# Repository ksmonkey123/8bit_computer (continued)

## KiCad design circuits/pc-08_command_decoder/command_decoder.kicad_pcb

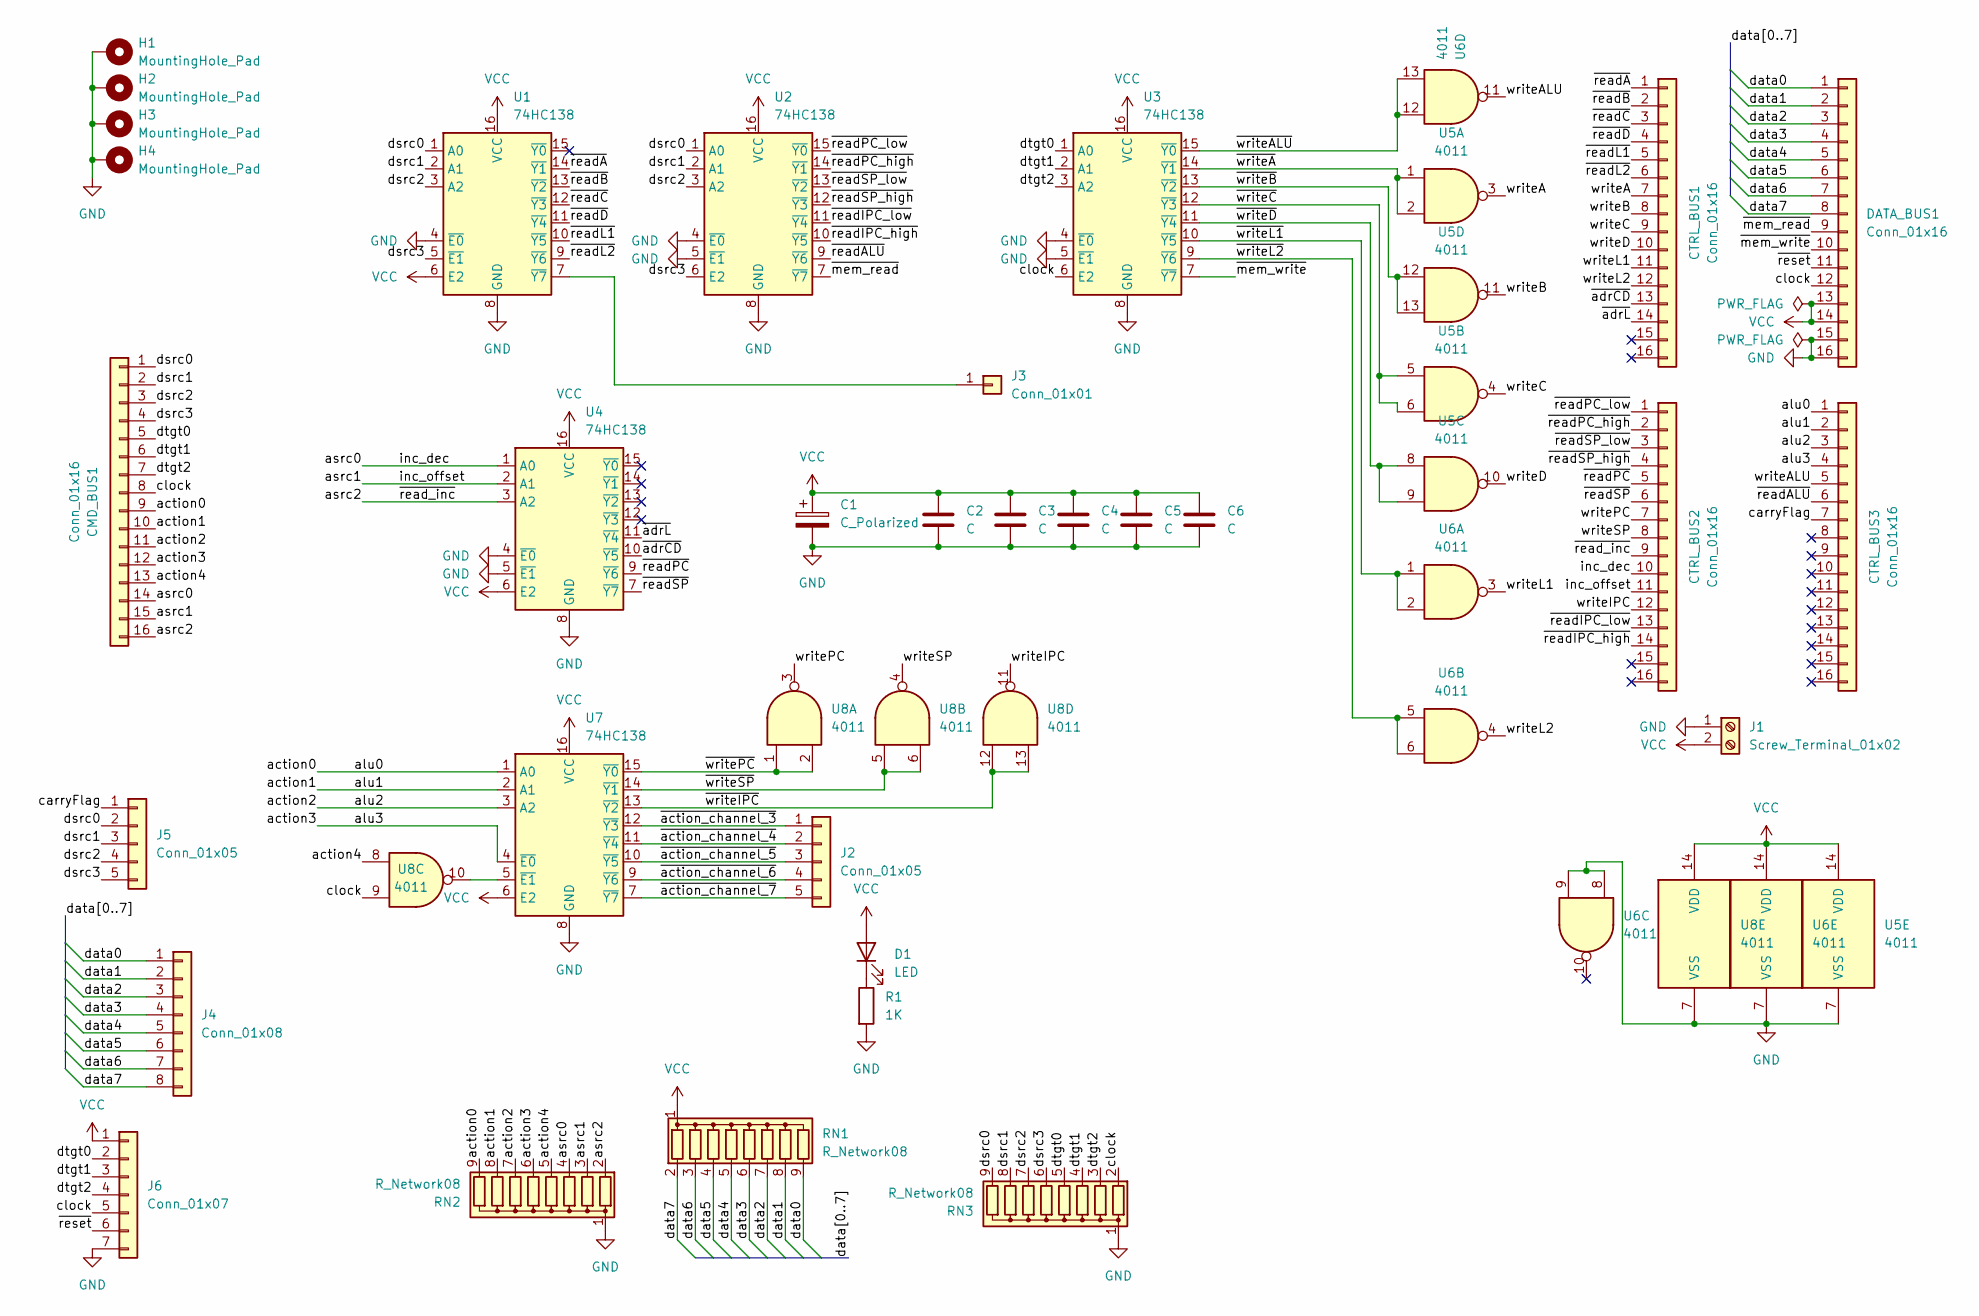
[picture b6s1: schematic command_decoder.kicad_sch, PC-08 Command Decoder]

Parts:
C1: C_Polarized; CP_Elec_5x5.3
C2, C3, C4, C5, C6: C; C_0603_1608Metric
CMD_BUS1: Conn_01x16; IDC-Header_2x08_P2.54mm_Horizontal
CTRL_BUS1, CTRL_BUS2, CTRL_BUS3: Conn_01x16; IDC-Header_2x08_P2.54mm_Vertical
D1: LED; LED_0603_1608Metric
DATA_BUS1: Conn_01x16; IDC-Header_2x08_P2.54mm_Horizontal
H1, H2, H3, H4: MountingHole_Pad; MountingHole_3.2mm_M3_Pad_Via
J1: Screw_Terminal_01x02; TerminalBlock_TE_282834-2_1x02_P2.54mm_Horizontal
J2, J5: Conn_01x05; PinHeader_1x05_P2.54mm_Vertical
J3: Conn_01x01; PinHeader_1x01_P2.54mm_Vertical
J4: Conn_01x08; PinHeader_1x08_P2.54mm_Vertical
J6: Conn_01x07; PinHeader_1x07_P2.54mm_Vertical
R1: 1K; R_0603_1608Metric
RN1, RN2, RN3: R_Network08; R_Array_SIP9
U1, U2, U3, U4, U7: 74HC138; DIP-16_W7.62mm_LongPads
U5, U6, U8: 4011; DIP-14_W7.62mm_LongPads

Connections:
/action0: CMD_BUS1.9, CTRL_BUS3.1, RN2.9 (R8), U7.1 (A0)
/action1: CMD_BUS1.10, CTRL_BUS3.2, RN2.8 (R7), U7.2 (A1)
/action2: CMD_BUS1.11, CTRL_BUS3.3, RN2.7 (R6), U7.3 (A2)
/action3: CMD_BUS1.12, CTRL_BUS3.4, RN2.6 (R5), U7.4 (~E0)
/action4: CMD_BUS1.13, RN2.5 (R4), U8.8
/asrc0: CMD_BUS1.14, CTRL_BUS2.10, RN2.4 (R3), U4.1 (A0)
/asrc1: CMD_BUS1.15, CTRL_BUS2.11, RN2.3 (R2), U4.2 (A1)
/asrc2: CMD_BUS1.16, CTRL_BUS2.9, RN2.2 (R1), U4.3 (A2)
/carryFlag: CTRL_BUS3.7, J5.1
/clock: CMD_BUS1.8, DATA_BUS1.12, J6.5, RN3.2 (R1), U3.6 (E2), U8.9
/data0: DATA_BUS1.1, J4.1, RN1.9 (R8)
/data1: DATA_BUS1.2, J4.2, RN1.8 (R7)
/data2: DATA_BUS1.3, J4.3, RN1.7 (R6)
/data3: DATA_BUS1.4, J4.4, RN1.6 (R5)
/data4: DATA_BUS1.5, J4.5, RN1.5 (R4)
/data5: DATA_BUS1.6, J4.6, RN1.4 (R3)
/data6: DATA_BUS1.7, J4.7, RN1.3 (R2)
/data7: DATA_BUS1.8, J4.8, RN1.2 (R1)
/dsrc0: CMD_BUS1.1, J5.2, RN3.9 (R8), U1.1 (A0), U2.1 (A0)
/dsrc1: CMD_BUS1.2, J5.3, RN3.8 (R7), U1.2 (A1), U2.2 (A1)
/dsrc2: CMD_BUS1.3, J5.4, RN3.7 (R6), U1.3 (A2), U2.3 (A2)
/dsrc3: CMD_BUS1.4, J5.5, RN3.6 (R5), U1.5 (~E1), U2.6 (E2)
/dtgt0: CMD_BUS1.5, J6.2, RN3.5 (R4), U3.1 (A0)
/dtgt1: CMD_BUS1.6, J6.3, RN3.4 (R3), U3.2 (A1)
/dtgt2: CMD_BUS1.7, J6.4, RN3.3 (R2), U3.3 (A2)
/writeA: CTRL_BUS1.7, U5.3
/writeALU: CTRL_BUS3.5, U6.11
/writeB: CTRL_BUS1.8, U5.11
/writeC: CTRL_BUS1.9, U5.4
/writeD: CTRL_BUS1.10, U5.10
/writeIPC: CTRL_BUS2.12, U8.11
/writeL1: CTRL_BUS1.11, U6.3
/writeL2: CTRL_BUS1.12, U6.4
/writePC: CTRL_BUS2.7, U8.3
/writeSP: CTRL_BUS2.8, U8.4
/~action_channel_3: J2.1, U7.12 (~Y3)
/~action_channel_4: J2.2, U7.11 (~Y4)
/~action_channel_5: J2.3, U7.10 (~Y5)
/~action_channel_6: J2.4, U7.9 (~Y6)
/~action_channel_7: J2.5, U7.7 (~Y7)
/~adrCD: CTRL_BUS1.13, U4.10 (~Y5)
/~adrL: CTRL_BUS1.14, U4.11 (~Y4)
/~mem_read: DATA_BUS1.9, U2.7 (~Y7)
/~mem_write: DATA_BUS1.10, U3.7 (~Y7)
/~readALU: CTRL_BUS3.6, U2.9 (~Y6)
/~readA: CTRL_BUS1.1, U1.14 (~Y1)
/~readB: CTRL_BUS1.2, U1.13 (~Y2)
/~readC: CTRL_BUS1.3, U1.12 (~Y3)
/~readD: CTRL_BUS1.4, U1.11 (~Y4)
/~readIPC_high: CTRL_BUS2.14, U2.10 (~Y5)
/~readIPC_low: CTRL_BUS2.13, U2.11 (~Y4)
/~readL1: CTRL_BUS1.5, U1.10 (~Y5)
/~readL2: CTRL_BUS1.6, U1.9 (~Y6)
/~readPC_high: CTRL_BUS2.2, U2.14 (~Y1)
/~readPC_low: CTRL_BUS2.1, U2.15 (~Y0)
/~readPC: CTRL_BUS2.5, U4.9 (~Y6)
/~readSP_high: CTRL_BUS2.4, U2.12 (~Y3)
/~readSP_low: CTRL_BUS2.3, U2.13 (~Y2)
/~readSP: CTRL_BUS2.6, U4.7 (~Y7)
/~reset: DATA_BUS1.11, J6.6
/~writeALU: U3.15 (~Y0), U6.12, U6.13
/~writeA: U3.14 (~Y1), U5.1, U5.2
/~writeB: U3.13 (~Y2), U5.12, U5.13
/~writeC: U3.12 (~Y3), U5.5, U5.6
/~writeD: U3.11 (~Y4), U5.8, U5.9
/~writeIPC: U7.13 (~Y2), U8.12, U8.13
/~writeL1: U3.10 (~Y5), U6.1, U6.2
/~writeL2: U3.9 (~Y6), U6.5, U6.6
/~writePC: U7.15 (~Y0), U8.1, U8.2
/~writeSP: U7.14 (~Y1), U8.5, U8.6
GND: C1.2, C2.2, C3.2, C4.2, C5.2, C6.2, DATA_BUS1.15, DATA_BUS1.16, H1.1, H2.1, H3.1, H4.1, J1.1, J6.7, R1.2, RN2.1 (common), RN3.1 (common), U1.4 (~E0), U1.8 (GND), U2.4 (~E0), U2.5 (~E1), U2.8 (GND), U3.4 (~E0), U3.5 (~E1), U3.8 (GND), U4.4 (~E0), U4.5 (~E1), U4.8 (GND), U5.7 (VSS), U6.7 (VSS), U6.8, U6.9, U7.8 (GND), U8.7 (VSS)
unnamed: D1.1 (K), R1.1
unnamed: J3.1, U1.7 (~Y7)
unnamed: U7.5 (~E1), U8.10
VCC: C1.1, C2.1, C3.1, C4.1, C5.1, C6.1, D1.2 (A), DATA_BUS1.13, DATA_BUS1.14, J1.2, J6.1, RN1.1 (common), U1.6 (E2), U1.16 (VCC), U2.16 (VCC), U3.16 (VCC), U4.6 (E2), U4.16 (VCC), U5.14 (VDD), U6.14 (VDD), U7.6 (E2), U7.16 (VCC), U8.14 (VDD)

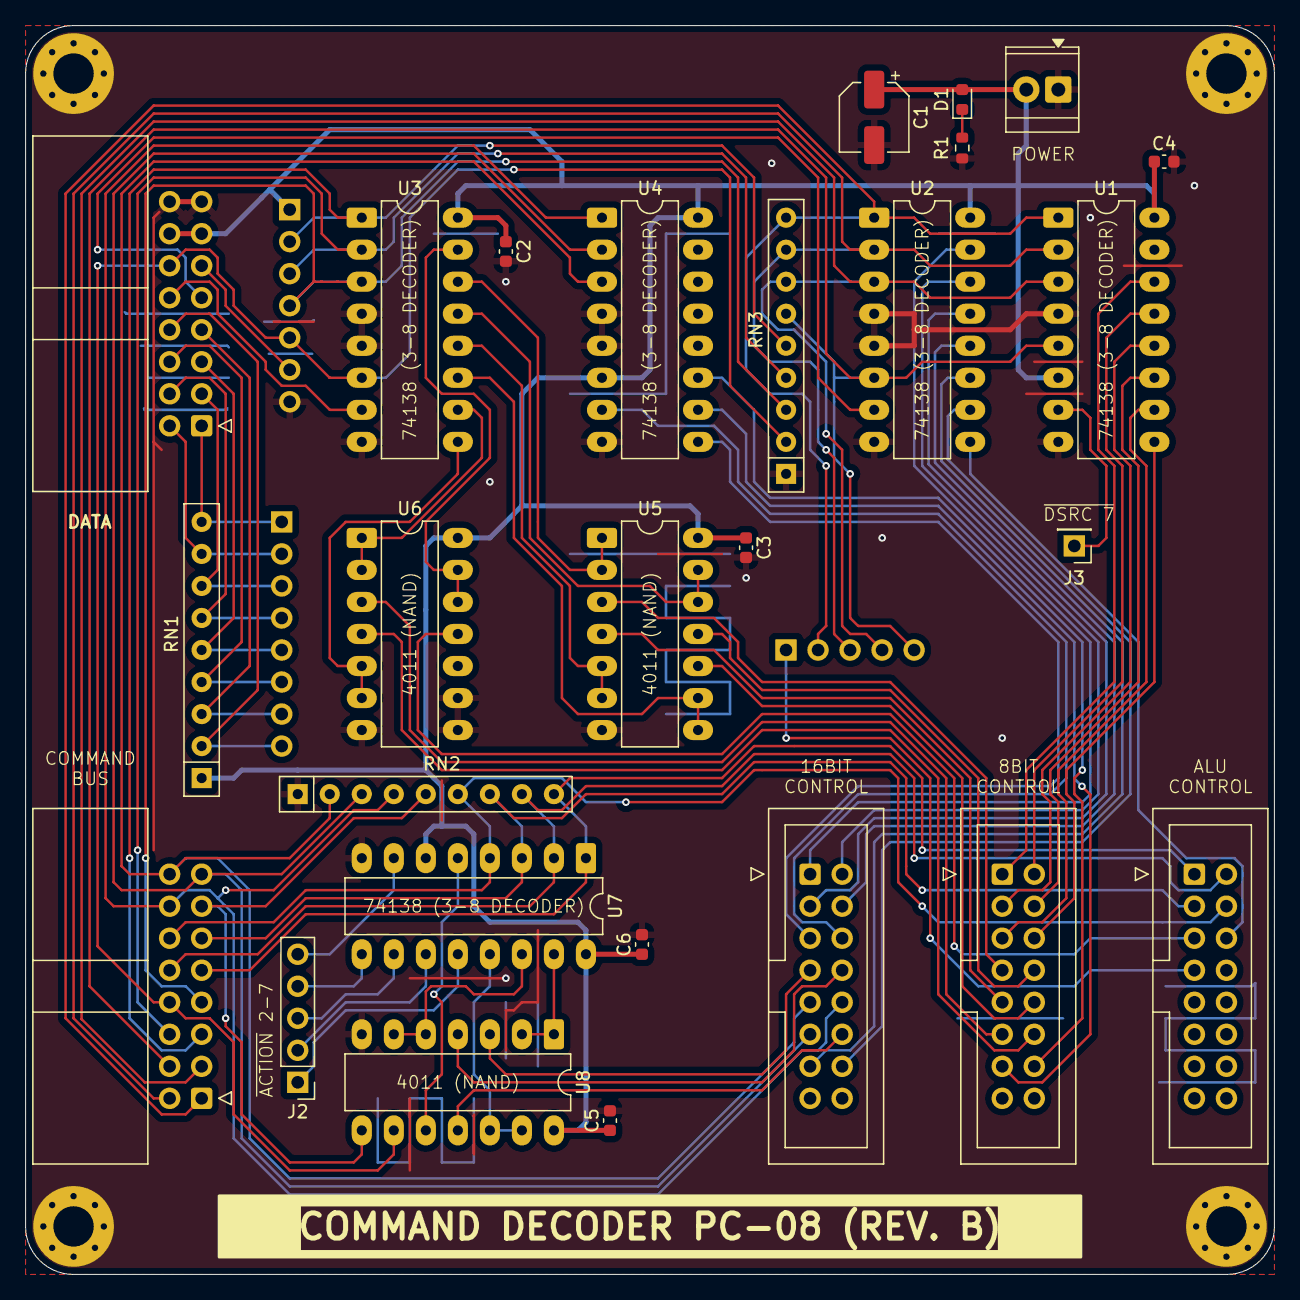
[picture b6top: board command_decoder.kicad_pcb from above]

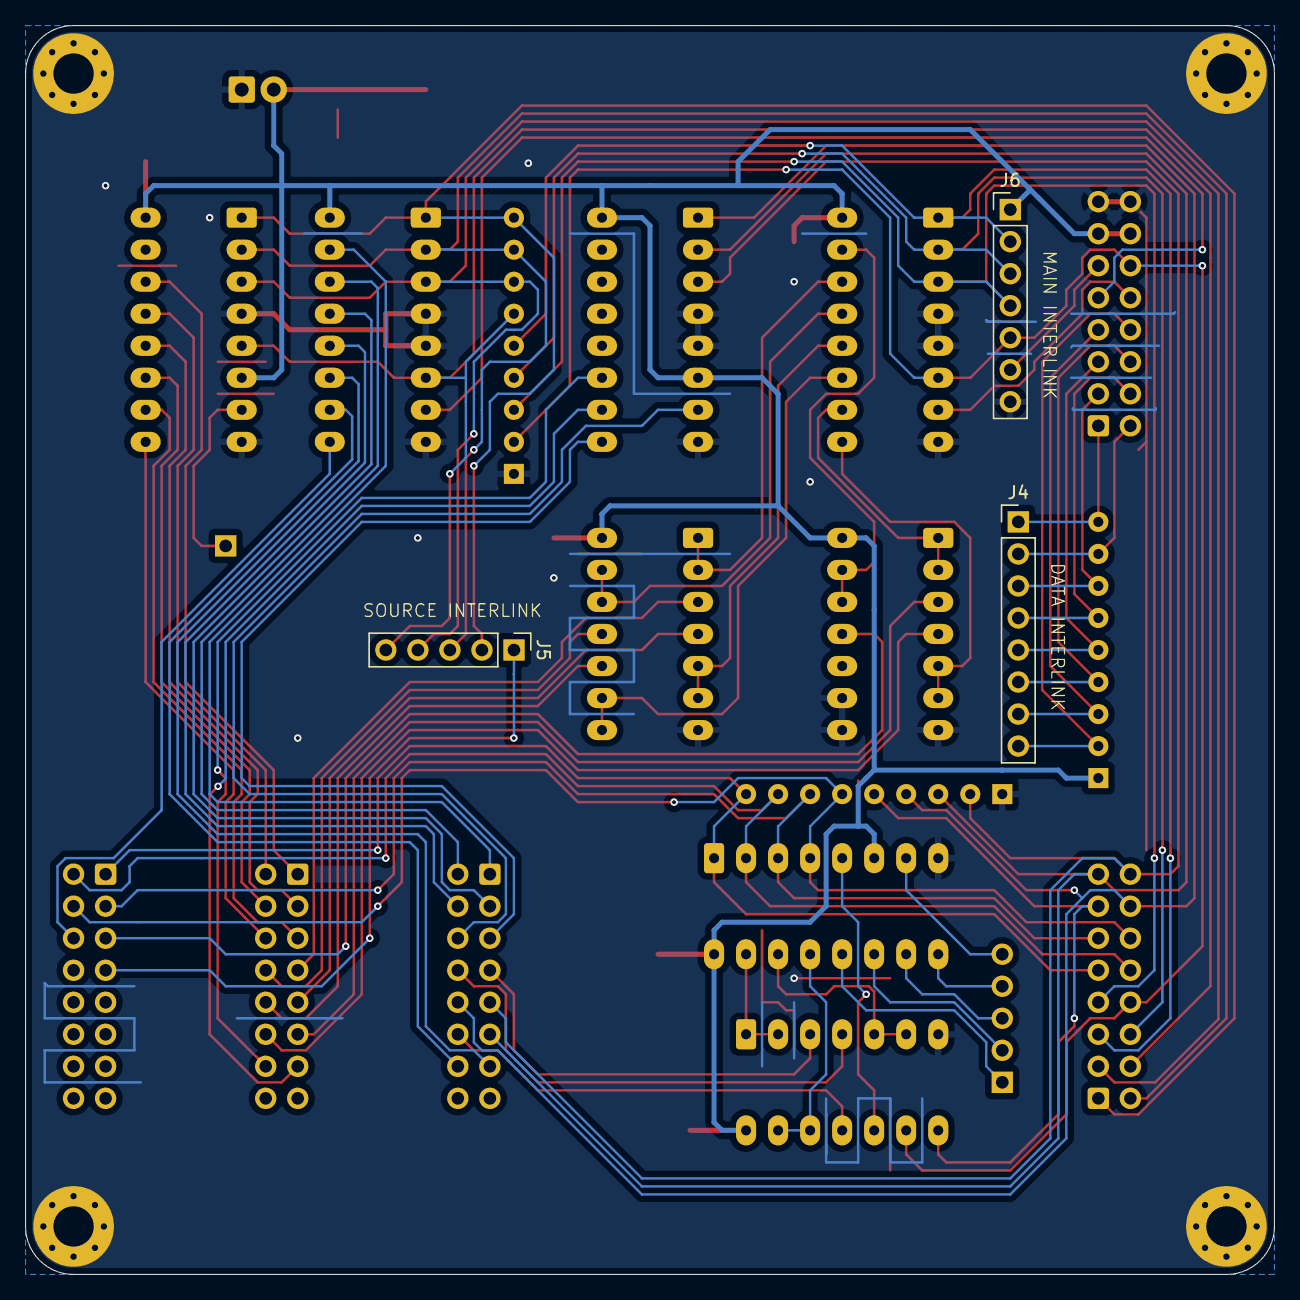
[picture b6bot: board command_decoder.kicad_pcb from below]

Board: 2 copper layers, 99.1 x 99.1 mm, 34 parts (3 on the bottom side), 75 nets.

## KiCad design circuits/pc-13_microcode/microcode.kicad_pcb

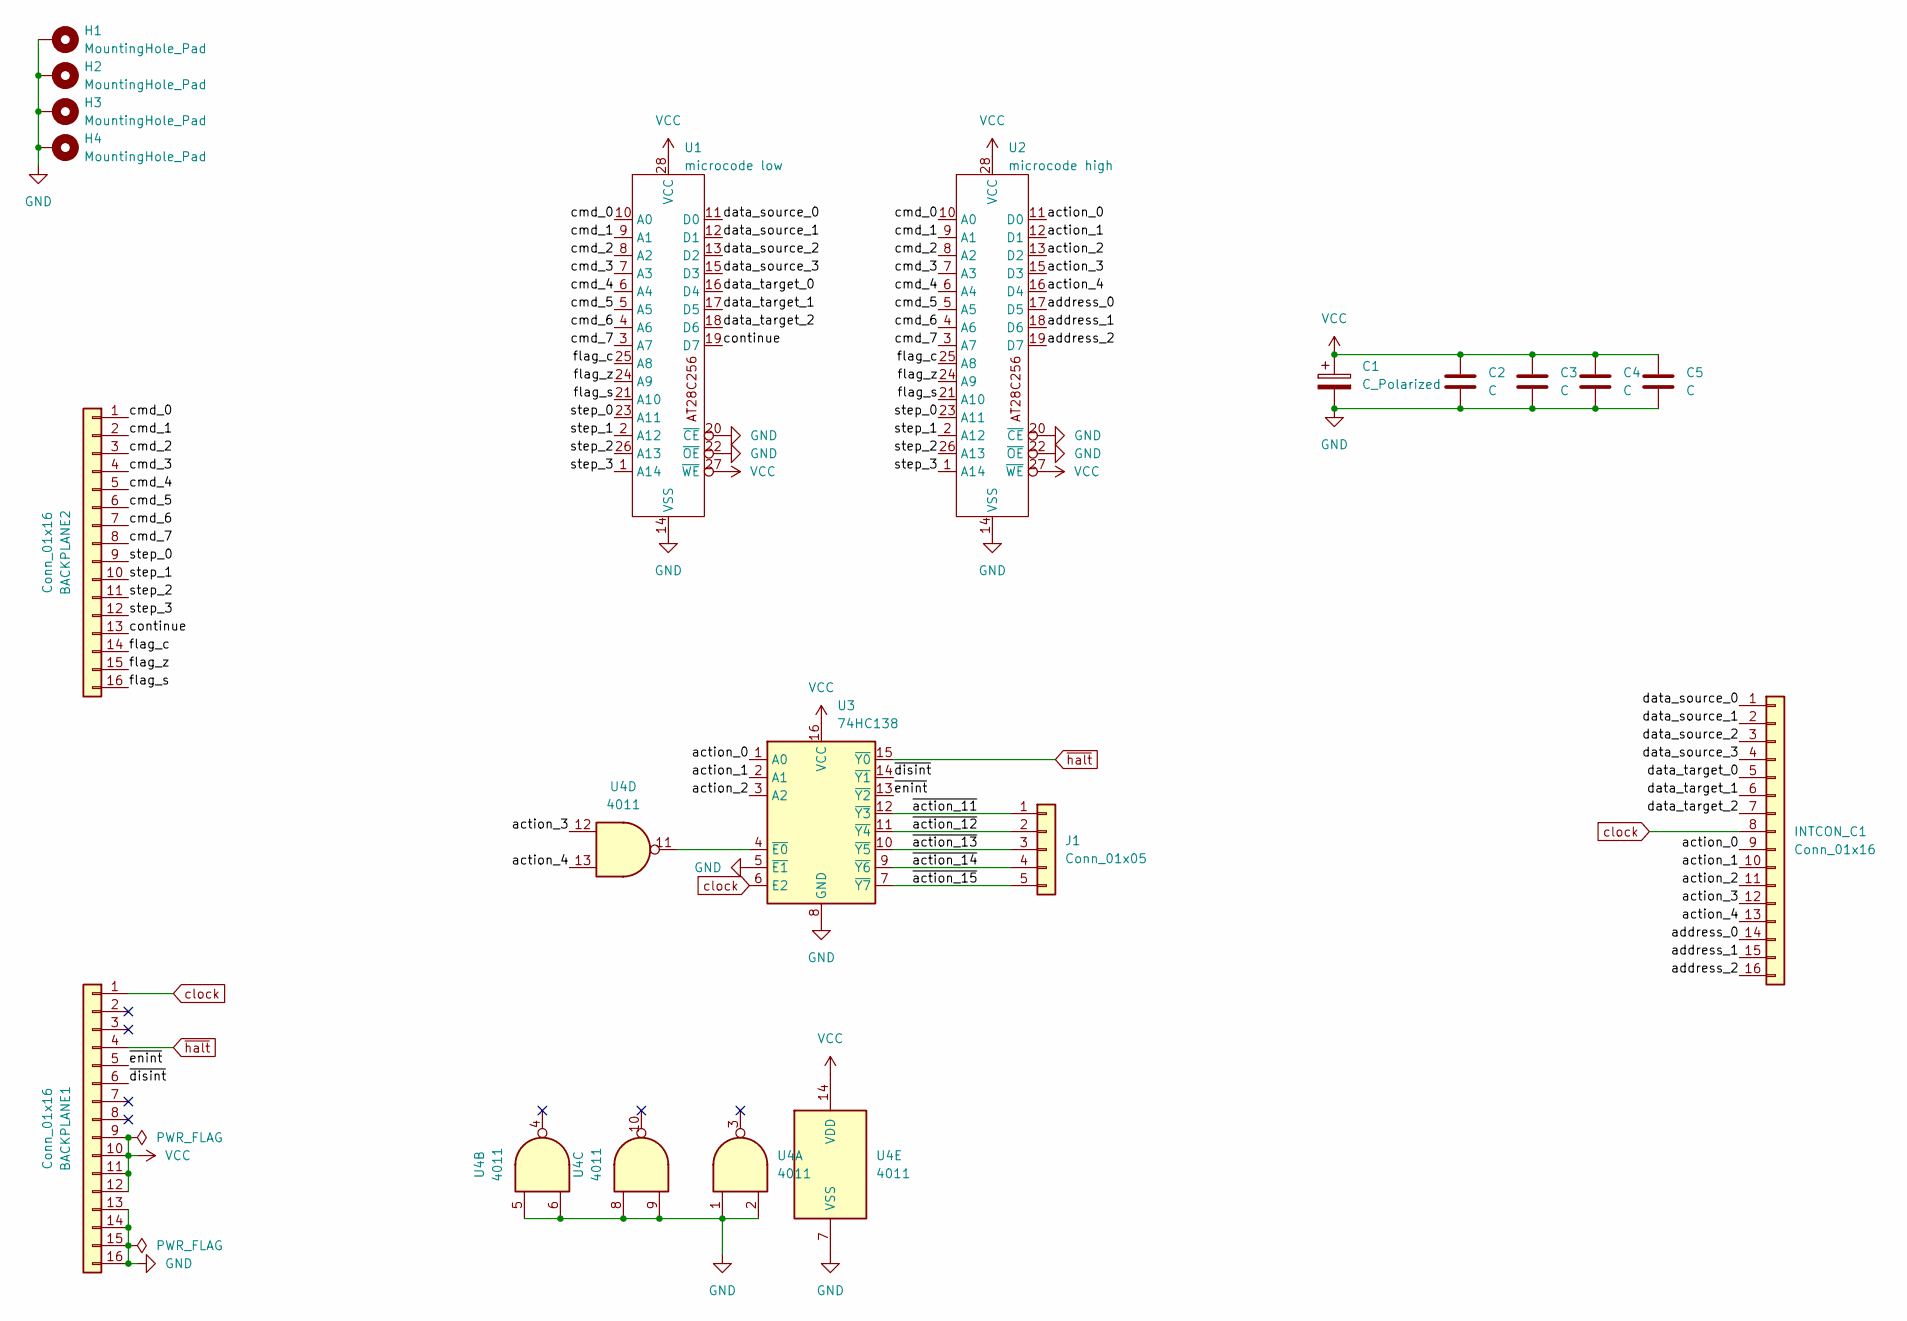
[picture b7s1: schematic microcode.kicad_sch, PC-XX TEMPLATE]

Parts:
BACKPLANE1, BACKPLANE2: Conn_01x16; IDC-Header_2x08_P2.54mm_Horizontal
C1: C_Polarized; CP_Elec_5x5.3
C2, C3, C4, C5: C; C_0603_1608Metric
H1, H2, H3, H4: MountingHole_Pad; MountingHole_3.2mm_M3_Pad_Via
INTCON_C1: Conn_01x16; IDC-Header_2x08_P2.54mm_Horizontal
J1: Conn_01x05; PinHeader_1x05_P2.54mm_Vertical
U1: microcode low; DIP-28_600_ELL
U2: microcode high; DIP-28_600_ELL
U3: 74HC138; DIP-16_W7.62mm
U4: 4011; DIP-14_W7.62mm

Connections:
/action_0: INTCON_C1.9, U2.11 (D0), U3.1 (A0)
/action_1: INTCON_C1.10, U2.12 (D1), U3.2 (A1)
/action_2: INTCON_C1.11, U2.13 (D2), U3.3 (A2)
/action_3: INTCON_C1.12, U2.15 (D3), U4.12
/action_4: INTCON_C1.13, U2.16 (D4), U4.13
/address_0: INTCON_C1.14, U2.17 (D5)
/address_1: INTCON_C1.15, U2.18 (D6)
/address_2: INTCON_C1.16, U2.19 (D7)
/cmd_0: BACKPLANE2.1, U1.10 (A0), U2.10 (A0)
/cmd_1: BACKPLANE2.2, U1.9 (A1), U2.9 (A1)
/cmd_2: BACKPLANE2.3, U1.8 (A2), U2.8 (A2)
/cmd_3: BACKPLANE2.4, U1.7 (A3), U2.7 (A3)
/cmd_4: BACKPLANE2.5, U1.6 (A4), U2.6 (A4)
/cmd_5: BACKPLANE2.6, U1.5 (A5), U2.5 (A5)
/cmd_6: BACKPLANE2.7, U1.4 (A6), U2.4 (A6)
/cmd_7: BACKPLANE2.8, U1.3 (A7), U2.3 (A7)
/continue: BACKPLANE2.13, U1.19 (D7)
/data_source_0: INTCON_C1.1, U1.11 (D0)
/data_source_1: INTCON_C1.2, U1.12 (D1)
/data_source_2: INTCON_C1.3, U1.13 (D2)
/data_source_3: INTCON_C1.4, U1.15 (D3)
/data_target_0: INTCON_C1.5, U1.16 (D4)
/data_target_1: INTCON_C1.6, U1.17 (D5)
/data_target_2: INTCON_C1.7, U1.18 (D6)
/flag_c: BACKPLANE2.14, U1.25 (A8), U2.25 (A8)
/flag_s: BACKPLANE2.16, U1.21 (A10), U2.21 (A10)
/flag_z: BACKPLANE2.15, U1.24 (A9), U2.24 (A9)
/step_0: BACKPLANE2.9, U1.23 (A11), U2.23 (A11)
/step_1: BACKPLANE2.10, U1.2 (A12), U2.2 (A12)
/step_2: BACKPLANE2.11, U1.26 (A13), U2.26 (A13)
/step_3: BACKPLANE2.12, U1.1 (A14), U2.1 (A14)
/~action_11: J1.1, U3.12 (~Y3)
/~action_12: J1.2, U3.11 (~Y4)
/~action_13: J1.3, U3.10 (~Y5)
/~action_14: J1.4, U3.9 (~Y6)
/~action_15: J1.5, U3.7 (~Y7)
/~disint: BACKPLANE1.6, U3.14 (~Y1)
/~enint: BACKPLANE1.5, U3.13 (~Y2)
GND: BACKPLANE1.13, BACKPLANE1.14, BACKPLANE1.15, BACKPLANE1.16, C1.2, C2.2, C3.2, C4.2, C5.2, H1.1, H2.1, H3.1, H4.1, U1.14 (VSS), U1.20 (~CE), U1.22 (~OE), U2.14 (VSS), U2.20 (~CE), U2.22 (~OE), U3.5 (~E1), U3.8 (GND), U4.1, U4.2, U4.5, U4.6, U4.7 (VSS), U4.8, U4.9
unnamed: U3.4 (~E0), U4.11
VCC: BACKPLANE1.9, BACKPLANE1.10, BACKPLANE1.11, BACKPLANE1.12, C1.1, C2.1, C3.1, C4.1, C5.1, U1.27 (~WE), U1.28 (VCC), U2.27 (~WE), U2.28 (VCC), U3.16 (VCC), U4.14 (VDD)
clock: BACKPLANE1.1, INTCON_C1.8, U3.6 (E2)
~halt: BACKPLANE1.4, U3.15 (~Y0)

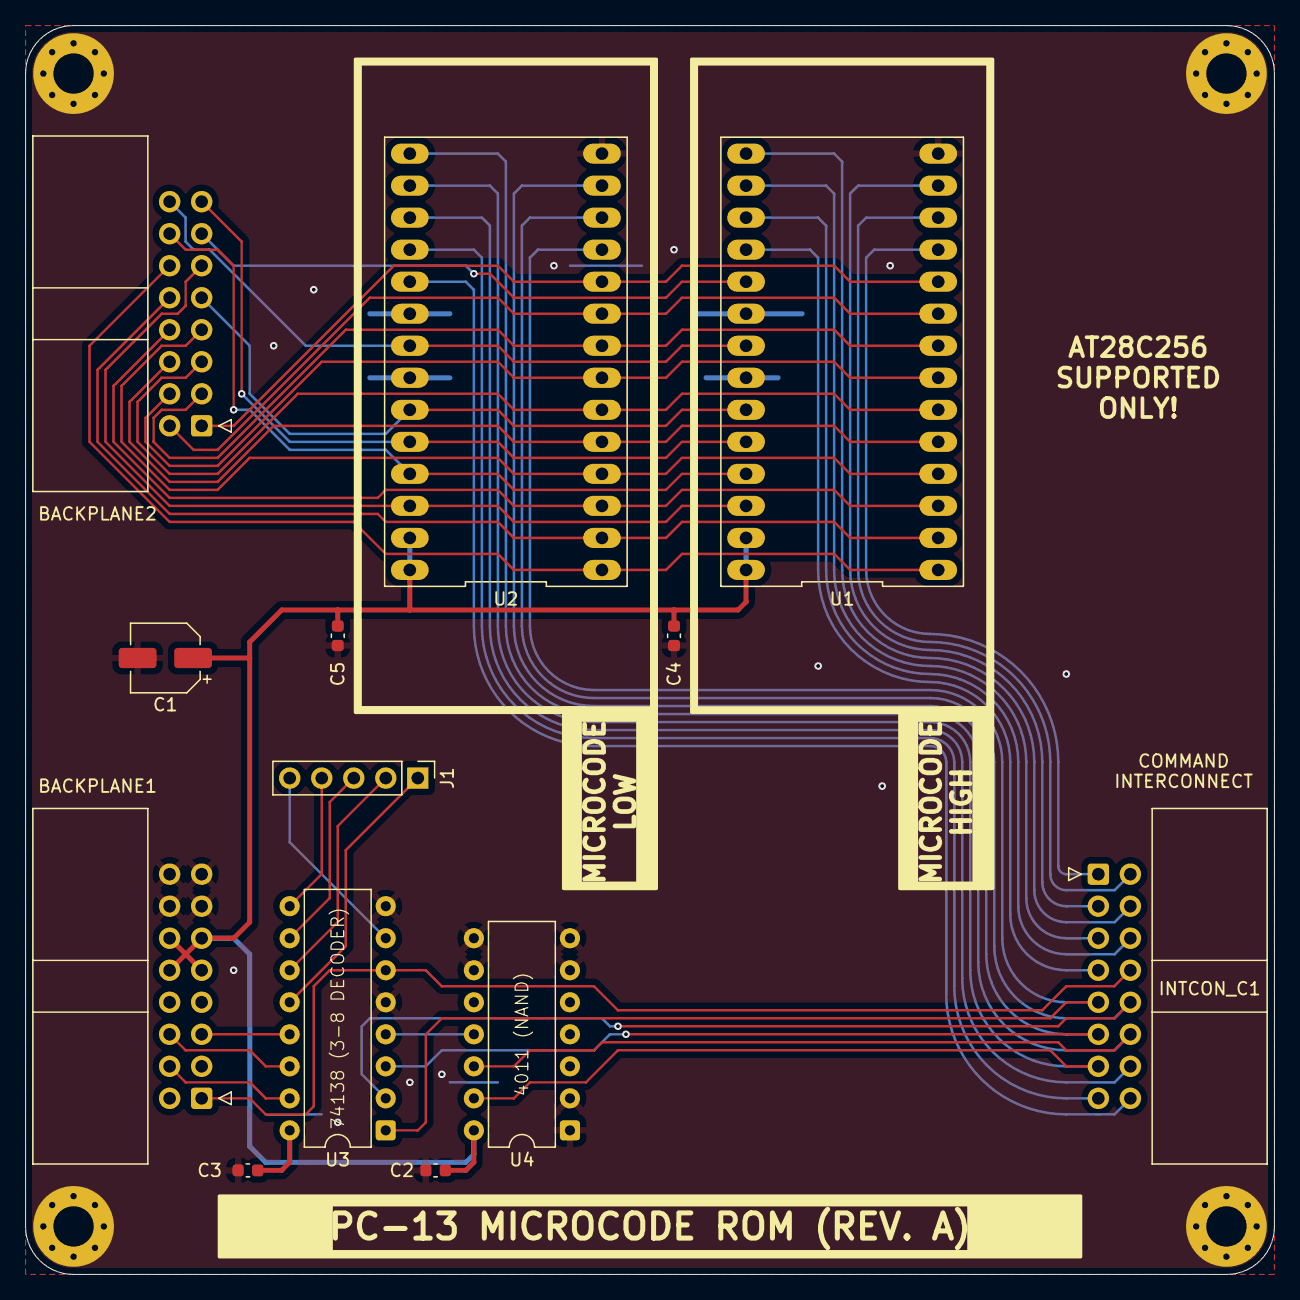
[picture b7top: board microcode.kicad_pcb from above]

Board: 2 copper layers, 99.1 x 99.1 mm, 17 parts (0 on the bottom side), 43 nets.

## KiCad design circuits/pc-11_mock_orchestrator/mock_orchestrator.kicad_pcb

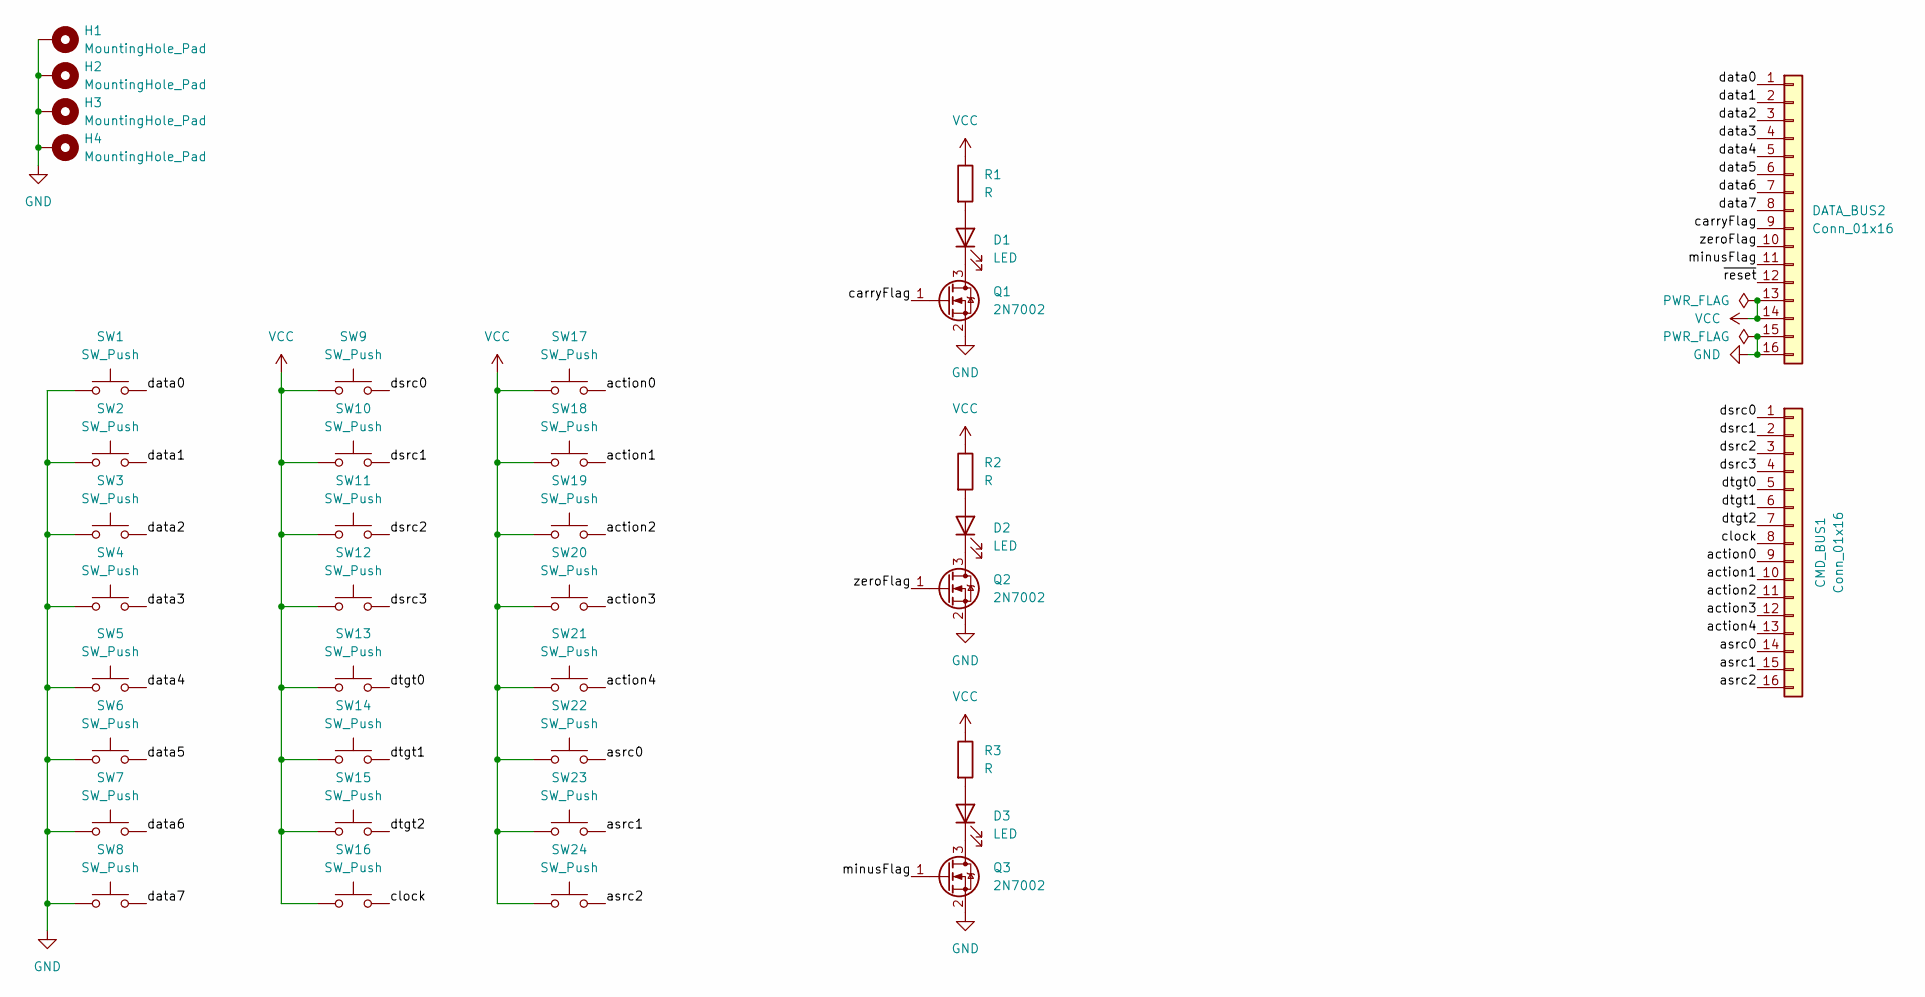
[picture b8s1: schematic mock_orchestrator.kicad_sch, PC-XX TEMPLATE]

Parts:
CMD_BUS1: Conn_01x16; IDC-Header_2x08_P2.54mm_Vertical
D1, D2, D3: LED; LED_0603_1608Metric
DATA_BUS2: Conn_01x16; IDC-Header_2x08_P2.54mm_Vertical
H1, H2, H3, H4: MountingHole_Pad; MountingHole_3.2mm_M3_Pad_Via
Q1, Q2, Q3: 2N7002; SOT-23
R1, R2, R3: R; R_0603_1608Metric
SW1, SW2, SW3, SW4, SW5, SW6, SW7, SW8, SW9, SW10, SW11, SW12, SW13, SW14, SW15, SW16, SW17, SW18, SW19, SW20, SW21, SW22, SW23, SW24: SW_Push; SW_PUSH_6mm

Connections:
/action0: CMD_BUS1.9, SW17.2
/action1: CMD_BUS1.10, SW18.2
/action2: CMD_BUS1.11, SW19.2
/action3: CMD_BUS1.12, SW20.2
/action4: CMD_BUS1.13, SW21.2
/asrc0: CMD_BUS1.14, SW22.2
/asrc1: CMD_BUS1.15, SW23.2
/asrc2: CMD_BUS1.16, SW24.2
/carryFlag: DATA_BUS2.9, Q1.1 (G)
/clock: CMD_BUS1.8, SW16.2
/data0: DATA_BUS2.1, SW1.2
/data1: DATA_BUS2.2, SW2.2
/data2: DATA_BUS2.3, SW3.2
/data3: DATA_BUS2.4, SW4.2
/data4: DATA_BUS2.5, SW5.2
/data5: DATA_BUS2.6, SW6.2
/data6: DATA_BUS2.7, SW7.2
/data7: DATA_BUS2.8, SW8.2
/dsrc0: CMD_BUS1.1, SW9.2
/dsrc1: CMD_BUS1.2, SW10.2
/dsrc2: CMD_BUS1.3, SW11.2
/dsrc3: CMD_BUS1.4, SW12.2
/dtgt0: CMD_BUS1.5, SW13.2
/dtgt1: CMD_BUS1.6, SW14.2
/dtgt2: CMD_BUS1.7, SW15.2
/minusFlag: DATA_BUS2.11, Q3.1 (G)
/zeroFlag: DATA_BUS2.10, Q2.1 (G)
/~reset: DATA_BUS2.12
GND: DATA_BUS2.15, DATA_BUS2.16, H1.1, H2.1, H3.1, H4.1, Q1.2 (S), Q2.2 (S), Q3.2 (S), SW1.1, SW2.1, SW3.1, SW4.1, SW5.1, SW6.1, SW7.1, SW8.1
unnamed: D1.2 (A), R1.2
unnamed: D1.1 (K), Q1.3 (D)
unnamed: D2.2 (A), R2.2
unnamed: D2.1 (K), Q2.3 (D)
unnamed: D3.2 (A), R3.2
unnamed: D3.1 (K), Q3.3 (D)
VCC: DATA_BUS2.13, DATA_BUS2.14, R1.1, R2.1, R3.1, SW9.1, SW10.1, SW11.1, SW12.1, SW13.1, SW14.1, SW15.1, SW16.1, SW17.1, SW18.1, SW19.1, SW20.1, SW21.1, SW22.1, SW23.1, SW24.1

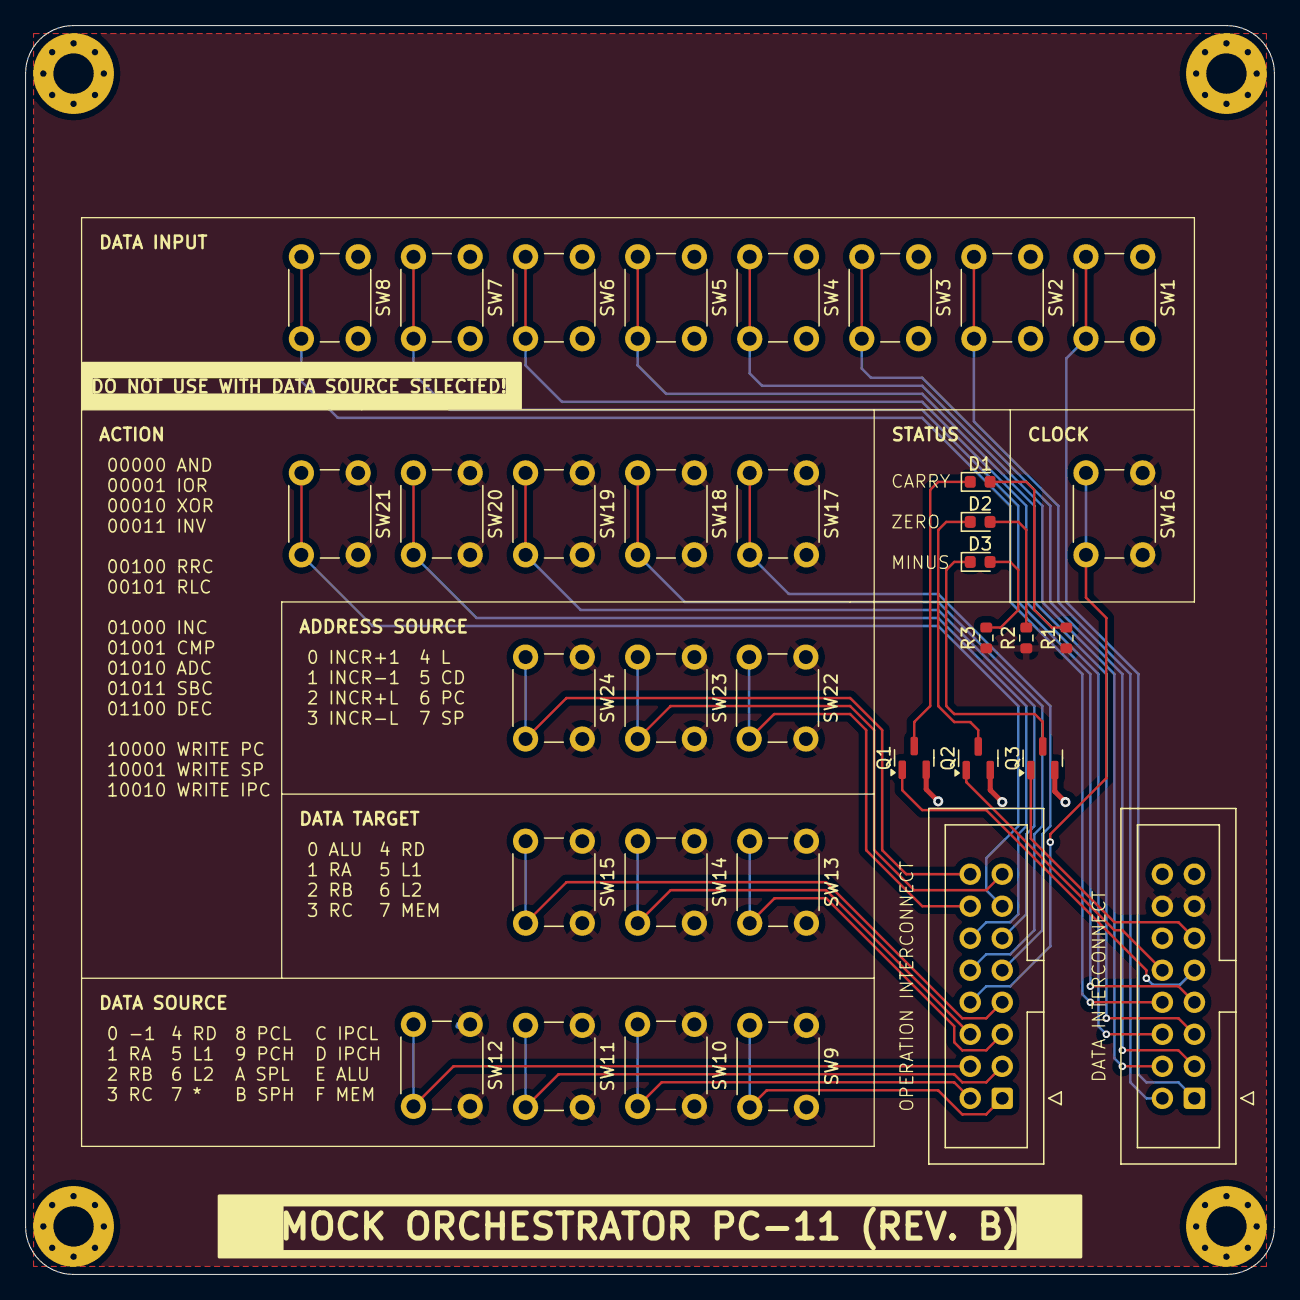
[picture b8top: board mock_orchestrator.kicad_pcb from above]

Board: 2 copper layers, 99.1 x 99.1 mm, 39 parts (0 on the bottom side), 35 nets.

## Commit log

2024-12-10 add gitignore
2024-12-10 add emulator project
2024-12-10 emulator: data bus and general purpose register modelling
2024-12-13 emulator: started new tick based model.
2024-12-13 emulator: first component: 32bit data bus
2024-12-13 emulator: improved tests
2024-12-13 emulator: kotlin upgrade
2024-12-15 emulator: add bus derived signal (extracting a single bit from a data bus)
2024-12-15 emulator: add datasignal as a single-bit version of the data bus
2024-12-15 emulator: add helper method to DataBus for generating a signal wire
2024-12-15 emulator: add tests
2024-12-15 emulator: reworked bus logic
2024-12-15 emulator: add IC 74273
2024-12-16 emulator: fix IC 74273 considering higher order bytes
2024-12-16 emulator: add byte bus (dataBus extracting a single byte out of a normal bus and providing it as the lowest byte)
2024-12-16 emulator: move busDerivedSignal to interface
2024-12-16 emulator: add busCombiner
2024-12-16 emulator: introduce wiring package
2024-12-16 emulator: writableSignal and writableBus as interface (simpler testing)
2024-12-16 emulator: octal driver impl
2024-12-16 emulator: support nested components. useful for prebuilt composites
2024-12-16 emulator: simulationElement tick method optional
2024-12-17 emulator: add register
2024-12-17 emulator: drop IC codes from class names
2024-12-17 emulator: fix broken register test
2024-12-17 emulator: added full adder
2024-12-17 emulator: formatting
2024-12-17 emulator: add bus Xor
2024-12-19 emulator: add bus gate combining 2 busses with a logic operation
2024-12-19 emulator: add nand
2024-12-19 emulator: add decoder
2024-12-19 emulator: draft Logic Unit
2024-12-19 emulator: add possibility to name elements
2024-12-23 emulator: add constant bus and data signal
2024-12-23 emulator: add signal derived bus
2024-12-23 emulator: add helper for signal edge detection
2024-12-23 emulator: add jk-flipflop (with inverted k-signal to represent the 74109 IC)
2024-12-23 emulator: add roll unit
2024-12-24 emulator: add sequencer. renamed 'components' to 'modules'
2024-12-24 emulator: restructured modules into sub-packages to better group them
2024-12-24 emulator: sub-component naming for all modules
2024-12-30 Add Datasheets
2024-12-30 Sequencer Schematic
2024-12-30 emulator: rename sequencer to stepSequencer
2024-12-30 emulator: add full sequencer unit
2024-12-30 emulator: add substep sequencer
2024-12-30 emulator: sequencer unit should treat a fetch size of 2 (`0b10`) as 0 (`0b00`).
2024-12-30 emulator: rename bit/byte helpers on bus
2024-12-30 emulator: add signal choice "IC" implementing 1-bit ternary z?y:x
2024-12-30 emulator: add math unit
2024-12-30 emulator: alu control circuit
2024-12-31 emulator: add ALU
2025-01-06 started design document
2025-01-06 emulator: sequencer only goes to 13 now (skipping substeps 2 and 3 in execution step)
2025-01-06 emulator: 16-bit bus driver
2025-01-06 emulator: design document revision - high-range operations reordered to allow for 0xff to be a no-op instruction
2025-01-07 emulator: quad register unit
2025-01-07 emulator: package renaming
2025-01-08 Create firmware.ino
    first version of programmer firmware. supports simple read and write commands
2025-01-08 microcode generator
2025-01-10 programmer firmware: sync support, higher baud rate
2025-01-10 eeprom programmer POC
2025-01-13 eeprom programmer moved to separate repo https://github.com/ksmonkey123/eeprom-programmer
2025-01-14 explicit alu instruction encoded into fetch code. (high nibble)
    allows for future re-arrangement
2025-01-14 move cmp/cmpc/ladd/lsub
2025-01-14 move entire 0x90 block to 0x80
2025-01-14 add explicit nop instruction
2025-01-14 move mov to 0x80 block. all alu operations move down one block. this groups all ALU operations into the lower half of the address space
2025-01-14 compact branching. move high blocks left to remove gap after ALU operations.
2025-01-14 update emulator microcode
2025-01-14 fix bad opcode compilation
2025-01-14 move cycle flag to address pin 12
2025-01-14 ALU literal support
2025-01-14 ALU rework
2025-01-14 add root aggregator pom allowing future dependencies between modules
2025-01-14 add ROM chip
2025-01-14 add clock "chip"
2025-01-14 reworked instruction table in document. fixed bad ALU decoding for roll unit and 2s complement
2025-01-14 documentation
2025-01-16 add basic hardware stack pointer
2025-01-20 new microcode
2025-01-20 create new emulator and assembler modules
2025-01-20 rename emulator module to hardware
2025-01-20 add HALT instruction to instruction set
2025-01-20 package renaming
2025-01-22 first draft of software emulator
2025-01-22 rework of ALU structure. start new instruction set. start single-command tests
2025-01-23 add tests for 0x10:1f commands (including implementation and instruction set fixes)
2025-01-23 add tests for range 0x20:3f
2025-01-24 add tests for range 0x40:4f (and fixes in inc / dec microcode)
2025-01-24 small refactoring of class structures
2025-01-24 fix spring dependencies in microcode building invalid library JAR
2025-01-26 comp / compc tests
2025-01-26 mov / load / store tests
2025-01-26 add 16bit load and store operations
2025-01-26 add 16bit immediate load instructions
2025-01-26 add tests
2025-01-27 add 8bit stack push/pop/peek operations
2025-01-27 add branching commands
2025-01-28 add decrement with conditional branching
2025-01-28 start assembler grammar
2025-02-01 conversion from parsetree to AST for vars and code. data still missing
2025-02-02 add 16bit move and stack pointer operations
2025-02-02 remove arithmetic operations without carry
2025-02-02 remove decbnz
2025-02-02 fix fibonacci test
2025-02-02 adapt grammar for new instruction set
2025-02-02 add salloc and sfree instructions
2025-02-02 reworked move operations
2025-02-02 assembler rework
2025-02-03 instruction set rework
2025-02-03 data sections
2025-02-03 refactoring: mapping methods are moved to parser. AST is now pure
2025-02-03 swap command with memory
2025-02-03 start bytecode generation
2025-02-05 bytecode fragment generation
2025-02-05 assembler implementation. TODO: file I/O and CLI
2025-02-06 assembler cli
2025-02-06 fix bad opcode for 'jsr' instruction
2025-02-06 first emulator tests including assembler
2025-02-12 rework architecture and microcode to get rid of registers with multiple write sources.
    Each register is now either entirely written to via the address or the data bus
2025-02-17 assembler testing
2025-02-17 improved assembler
2025-02-17 pc-01 rev A: dual 8-bit register unit
2025-02-17 pc-02 rev A: 16bit register unit for PC and SP
2025-02-18 pc-03: increment unit rev a
2025-02-19 Instruction set rework: Carry flag is now a part of the ALU and only ever updated on ALU read. This allows for local handling of this flag. (this includes the removal of carry-flag initialisation dur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
2025-02-20 pc-04: alu backplane
2025-02-20 pcb template
2025-02-20 Kicad upgrade to 9.0
2025-02-20 starting with adder
2025-02-21 pc-04: add missing pull-up resistors
2025-02-21 pc-05: ALU adder prototype
2025-02-24 pc-05: polishing of adder circuit
2025-02-24 pc-06: alu logic unit
2025-02-25 pc-07: ram unit
2025-02-25 alu input write on fetch cycles
2025-02-26 pc-02: move decoder hardware onto board
2025-02-26 reworked microcode format
2025-02-26 pc-08: decoder unit
2025-02-26 add pull-up resistor network to command decoder
2025-02-26 pc08: finishing touches and interconnects
2025-02-27 pc09-orchestrator
2025-02-27 bus spy, mock orchestrator & cleanup
2025-02-28 add filter and decoupling capacitors to all boards
2025-02-28 cleanup
2025-02-28 final touches, pcb ordering
2025-03-04 pc-08 rework
2025-03-04 starting notes
2025-03-05 notes
2025-03-05 more documentation
2025-03-05 fix broken emulator
2025-03-05 update ALU microcode to new command structure
2025-03-05 update documentation for new revised step sequencing
2025-03-05 revised step sequencing
2025-03-07 documentation of physical connections
2025-03-10 unified sequencer
2025-03-10 use microcode model in emulator
2025-03-11 add logisim simulation
2025-10-24 documentaataion
2025-10-24 PC-08: fix incorrect dsrc silkscreen
    pin labels 12/13 were inverted.
2025-10-24 PC-03: fix incrementer unit
    * adders are TTL, the weak pull-down on the `inc_dec` signal was not enough to drive the 8 directly connected adder pins correctly. Fixed through the introduction of a non-inverting buffer on that si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
    * incorrect logic caused decrement mode (INCR-1) to calculate (INCR-1+1) by mistake. reworked logic by replacing the old CD4011 NAND by a CD4070 XOR.
2025-10-28 pc-03: add double buffering to incrementer unit
    This ensures stable data from the incrementer.
    Previously, the published address would change at the start of the write cycle.
    With the double buffering introduced, the current value of the address bus is latched into the first register at the start of the write cycle and pushed to the second register at the end of the write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
    This way the latched address is only seen by the incrementer at the start of the next cycle, ensuring a stable address bus state during the entire program step.
2025-10-28 PC-07: reworked RAM unit: falling edge of !mem_write signal is converted to a low-pulse.
    In experiments, 2 ceramic caps of 100nF each in series, and 2 resistors of 150 ohms yielded pulse widths of a just a few microseconds at clock rates of up to 25 kHz.
2025-10-28 pc-03: fix bad revision information on PCB layout sheet
2025-10-28 change simulation: double buffering on IR prevents potential issues on microcode ROM transitions at start of write cycle. microcode ROM addressing now only changes at the end of a cycle.
2025-10-28 simulation: add double buffering to flag signals to the microcode ROM. this ensures no ROM addressing transitions during a write cycle.
2025-10-28 unified instruction mnemonics
2025-10-28 rename instruction name map
2025-10-29 documentation upgrade
2025-10-29 fix assembler not working when `.vars` section is missing. (simple programs may not need it)
2025-10-29 migrate to a fully little-endian architecture. (inverts all 16-bit literals in assembled programs and inverts the fetch order of L1 and L2)
2025-10-29 convert simulation to little-endian microcode
2025-10-29 compile microcode for 32k ROMs and add 16-step instruction support to the emulator. (not yet supported by the microcode compiler)
2025-10-29 adapt microcode compiler for 16 step instructions
2025-10-29 reduce step count in some fetching instructions
2025-10-29 minor microcode compiler refactoring
2025-10-29 reduce step count for most instructions
2025-10-29 reduce step count for `JMP i16` and `RET`
2025-10-29 reduce step count for conditional branches
2025-10-29 add support for early terminating branches in instructions
2025-10-29 change 2 character mnemonics to 3 chars
2025-10-29 load improved microcode into pc simulation.
    the same fibonacci program ran ~12% faster.
2025-10-30 documentation update
2025-11-01 add IPC write to command decoder and 16-bit control bus.
    This signal may be used in the future for interrupt handling.
2025-11-02 start concept on interrupts
2025-11-11 modify assembler to produce variable size programs
2025-11-11 update documentation and update PCBs for interrupts
2025-11-11 add interrupt support in microcode and emulator
2025-11-11 add interrupt support to assembler. TODO: rework assembler & syntax
2025-11-12 simulation and documentation update for interrupts
2025-11-20 add sequencer
2025-11-21 microcode pcb
2025-11-22 pcb design
2025-11-23 reworking sequencer PCB
2025-11-24 finalize rev. a of pc-12
2025-11-24 temp
2025-11-24 pc-14: start clock module
2025-11-25 pc-14: continue clock module: full functionality and power-on reset logic.
2026-06-25 stack upgrade, generate microcode as hex files
2026-06-25 convert assembler to output hex files
2026-06-25 some sonar cleanups
2026-06-25 fix in logic for merging variable sections
